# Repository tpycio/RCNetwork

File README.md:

# Network Controller Designed For RC2014

This is a COM20020-based network controller board designed for the RC2014 microcomputer system. The module has been prepared for operation in the CP/Net local area network.

## Bill of Materials

Component type     | Reference  | Description                                  | Quantity |
------------------ | ---------- | -------------------------------------------- | -------- |
PCB                |            | Network Controller PCB - Version 1.1         | 1        |
Integrated Circuit | U1         | COM20020ILJP - Arcnet Controller,28 pin PLCC | 1        |
Integrated Circuit | U2         | SN75176 -  Bus Transceiver, 8 pin DIP        | 1        |
Integrated Circuit | U3         | 74HCT138 - 3-to-8 line decoder, 16 pin DIP   | 1        |
Crystal            | Q1         | 20 MHz, Crystal Oscillator, HC-49S           | 1        |
Diode TVS          | D1 - D3    | SD05C , SOT323                               | 3        |
Pin Header         | J1         | 40 pin header, 2.54 mm pitch, angle          | 1        |
Connector Contacts | J2, J3     | 3 pin header, WF-03R 2.54 mm pitch, angle    | 1        |
Capacitor          | C1, C2     | 27 pF, ceramic, 5 mm pitch                   | 2        |
Capacitor          | C3 - C6    | 0.1 uF, 50V, MLCC, 5 mm pitch                | 4        |
Resistor           | R1         | 10 kohm, 0.25 W, axial                       | 1        |
Resistor           | R2         | 120 ohm, 0.25 W, axial                       | 1        |
Resistor           | R3, R4, R7 | 10 ohm, 0.25 W, axial                        | 3        |
Resistor           | R5, R5     | 47 kohm, 0.25 W, axial                       | 2        |
IC Socket          | U1         | 28 pin PLCC, through hole                    | 1        |
IC Socket          | U2         | 8 pin DIP                                    | 1        |
IC Socket          | U5         | 16 pin DIP                                   | 1        |
Jumper             | JP1        | Shunt, 2x8 pin 2.54 mm pitch                 | 1        |
Jumper             | JP2        | Shunt, 3 pin 2.54 mm pitch                   | 1        |
Jumper             | JP3 - JP5  | Shunt, 2 pin 2.54 mm pitch                   | 3        |

## License

Copyright 2021 Tadeusz Pycio

This work is licensed under a [Creative Commons Attribution-ShareAlike 4.0 International License](http://creativecommons.org/licenses/by-sa/4.0/).

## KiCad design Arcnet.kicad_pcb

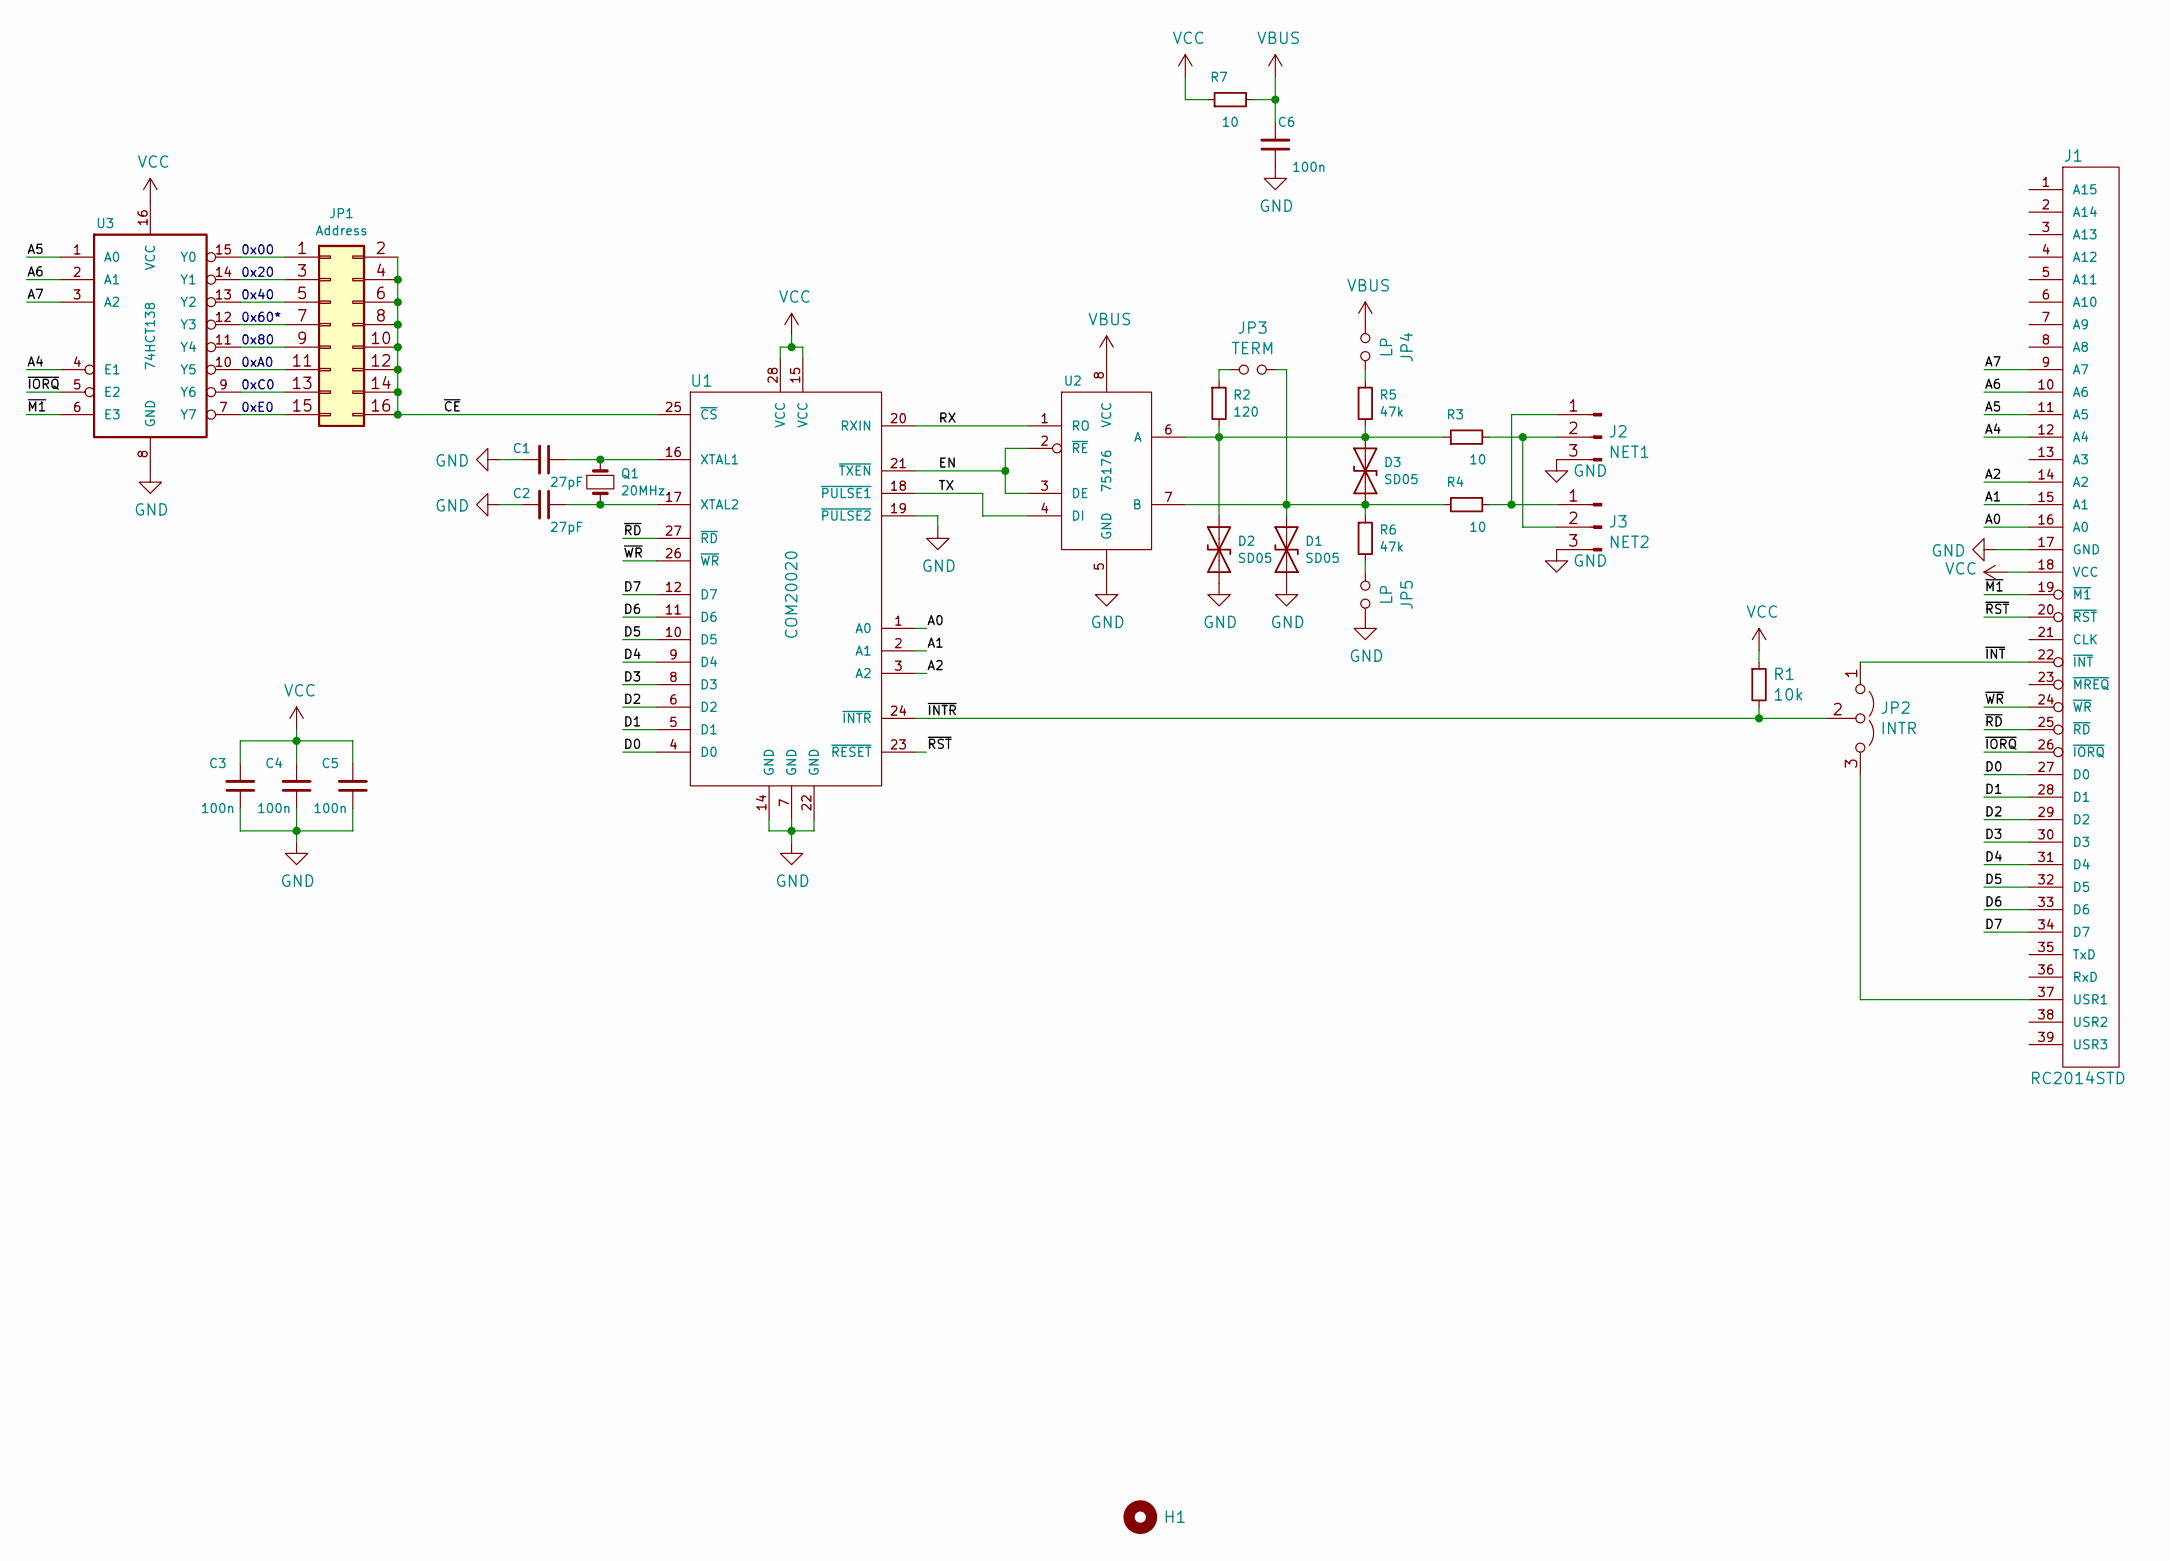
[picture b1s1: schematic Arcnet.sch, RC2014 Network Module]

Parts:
C1, C2: 27pF; C_Disc_D4.7mm_W2.5mm_P5.00mm
C3, C4, C5, C6: 100n; C_Disc_D4.7mm_W2.5mm_P5.00mm
D1, D2, D3: SD05; D_SOD-323_HandSolder
H1: MountingHole; MountingHole_3.2mm_M3_DIN965
J1: RC2014STD; PinHeader_1x39_P2.54mm_Vertical
J2: NET1; Molex_KK-254_AE-6410-03A_1x03_P2.54mm_Vertical
J3: NET2; Molex_KK-254_AE-6410-03A_1x03_P2.54mm_Vertical
JP1: Address; PinHeader_2x08_P2.54mm_Vertical
JP2: INTR; PinHeader_1x03_P2.54mm_Vertical
JP3: TERM; PinHeader_1x02_P2.54mm_Vertical
JP4, JP5: LP; PinHeader_1x02_P2.54mm_Vertical
Q1: 20MHz; Crystal_HC49-4H_Vertical
R1: 10k; R_Axial_DIN0207_L6.3mm_D2.5mm_P7.62mm_Horizontal
R2: 120; R_Axial_DIN0207_L6.3mm_D2.5mm_P7.62mm_Horizontal
R3, R4, R7: 10; R_Axial_DIN0207_L6.3mm_D2.5mm_P7.62mm_Horizontal
R5, R6: 47k; R_Axial_DIN0207_L6.3mm_D2.5mm_P7.62mm_Horizontal
U1: COM20020; PLCC-28_THT-Socket
U2: 75176; DIP-8_W7.62mm
U3: 74HCT138; DIP-16_W7.62mm

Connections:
/A0: J1.16 (A0), U1.1 (A0)
/A1: J1.15 (A1), U1.2 (A1)
/A2: J1.14 (A2), U1.3 (A2)
/A4: J1.12 (A4), U3.4 (E1)
/A5: J1.11 (A5), U3.1 (A0)
/A6: J1.10 (A6), U3.2 (A1)
/A7: J1.9 (A7), U3.3 (A2)
/D0: J1.27 (D0), U1.4 (D0)
/D1: J1.28 (D1), U1.5 (D1)
/D2: J1.29 (D2), U1.6 (D2)
/D3: J1.30 (D3), U1.8 (D3)
/D4: J1.31 (D4), U1.9 (D4)
/D5: J1.32 (D5), U1.10 (D5)
/D6: J1.33 (D6), U1.11 (D6)
/D7: J1.34 (D7), U1.12 (D7)
/EN: U1.21 (~TXEN), U2.2 (~RE), U2.3 (DE)
/RX: U1.20 (RXIN), U2.1 (RO)
/TX: U1.18 (~PULSE1), U2.4 (DI)
/~CE: JP1.2, JP1.4, JP1.6, JP1.8, JP1.10, JP1.12, JP1.14, JP1.16, U1.25 (~CS)
/~INT: J1.22 (~INT), JP2.1 (A)
/~INTR: JP2.2 (C), R1.2, U1.24 (~INTR)
/~IORQ: J1.26 (~IORQ), U3.5 (E2)
/~M1: J1.19 (~M1), U3.6 (E3)
/~RD: J1.25 (~RD), U1.27 (~RD)
/~RST: J1.20 (~RST), U1.23 (~RESET)
/~WR: J1.24 (~WR), U1.26 (~WR)
GND: C1.2, C2.2, C3.1, C4.1, C5.1, C6.1, D1.2 (A2), D2.2 (A2), J1.17 (GND), J2.3, J3.3, JP5.2, U1.7 (GND), U1.14 (GND), U1.19 (~PULSE2), U1.22 (GND), U2.5 (GND), U3.8 (GND)
unnamed: C1.1, Q1.1, U1.16 (XTAL1)
unnamed: C2.1, Q1.2, U1.17 (XTAL2)
unnamed: D1.1 (A1), D3.2 (A2), JP3.2, R4.2, R6.1, U2.7 (B)
unnamed: D2.1 (A1), D3.1 (A1), R2.2, R3.1, R5.2, U2.6 (A)
unnamed: J1.37 (USR1), JP2.3 (B)
unnamed: J2.1, J3.1, R4.1
unnamed: J2.2, J3.2, R3.2
unnamed: JP1.1, U3.15 (Y0)
unnamed: JP1.3, U3.14 (Y1)
unnamed: JP1.5, U3.13 (Y2)
unnamed: JP1.7, U3.12 (Y3)
unnamed: JP1.9, U3.11 (Y4)
unnamed: JP1.11, U3.10 (Y5)
unnamed: JP1.13, U3.9 (Y6)
unnamed: JP1.15, U3.7 (Y7)
unnamed: JP3.1, R2.1
unnamed: JP4.2, R5.1
unnamed: JP5.1, R6.2
VBUS: C6.2, JP4.1, R7.2, U2.8 (VCC)
VCC: C3.2, C4.2, C5.2, J1.18 (VCC), R1.1, R7.1, U1.15 (VCC), U1.28 (VCC), U3.16 (VCC)

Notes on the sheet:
0x00
0x20
0x40
0x60*
0x80
0xA0
0xC0
0xE0

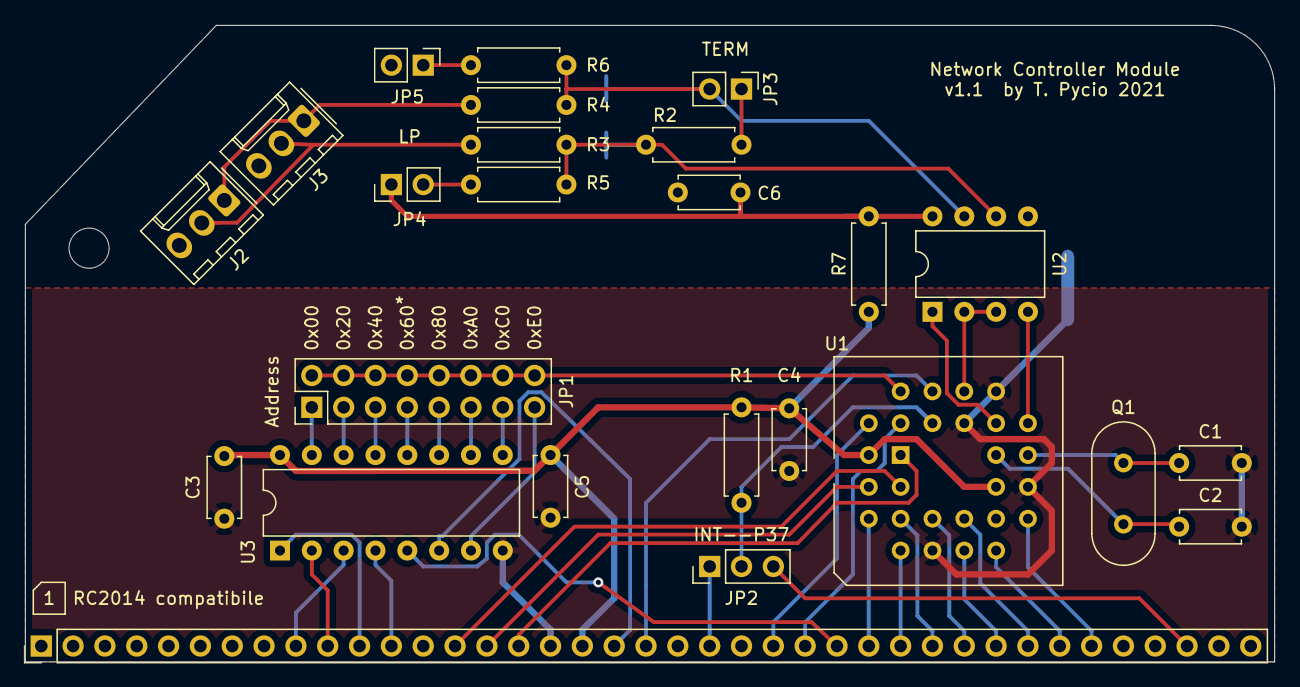
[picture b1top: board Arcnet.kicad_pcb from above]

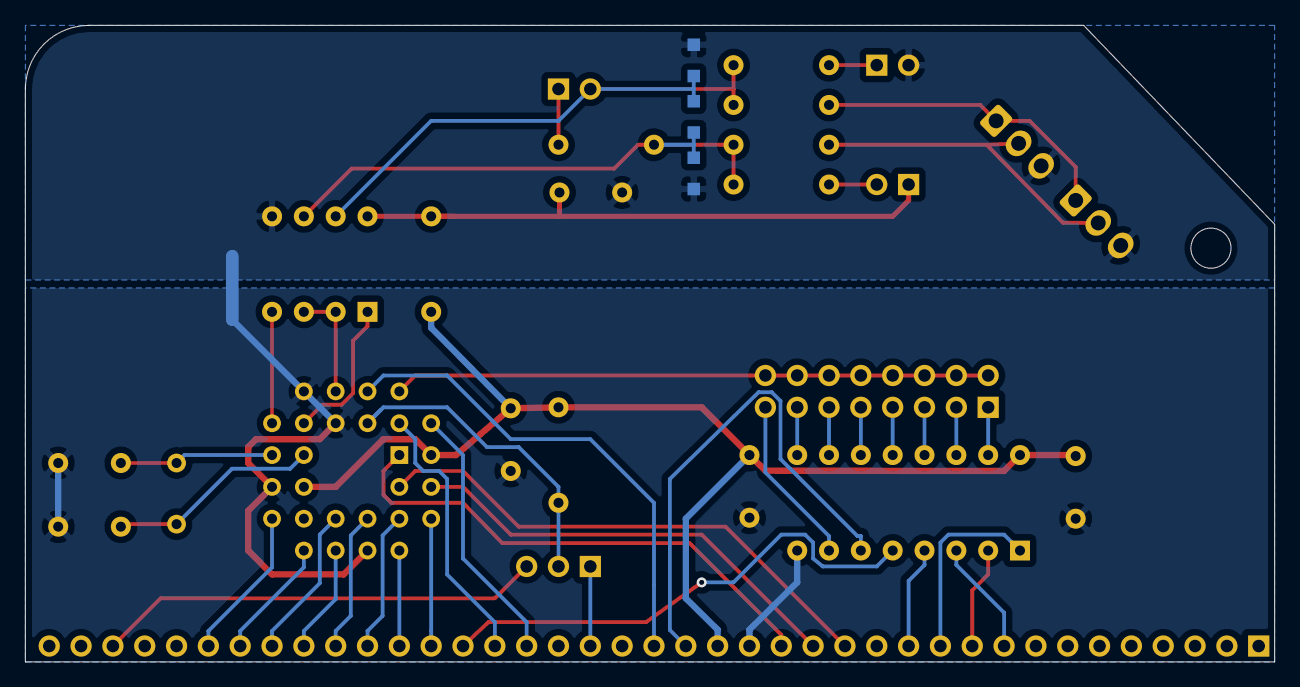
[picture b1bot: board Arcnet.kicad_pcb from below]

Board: 2 copper layers, 99.7 x 50.8 mm, 29 parts (3 on the bottom side), 47 nets.

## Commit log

2021-10-20 Network Controller for RC2014
    Network Controller for RC2014
